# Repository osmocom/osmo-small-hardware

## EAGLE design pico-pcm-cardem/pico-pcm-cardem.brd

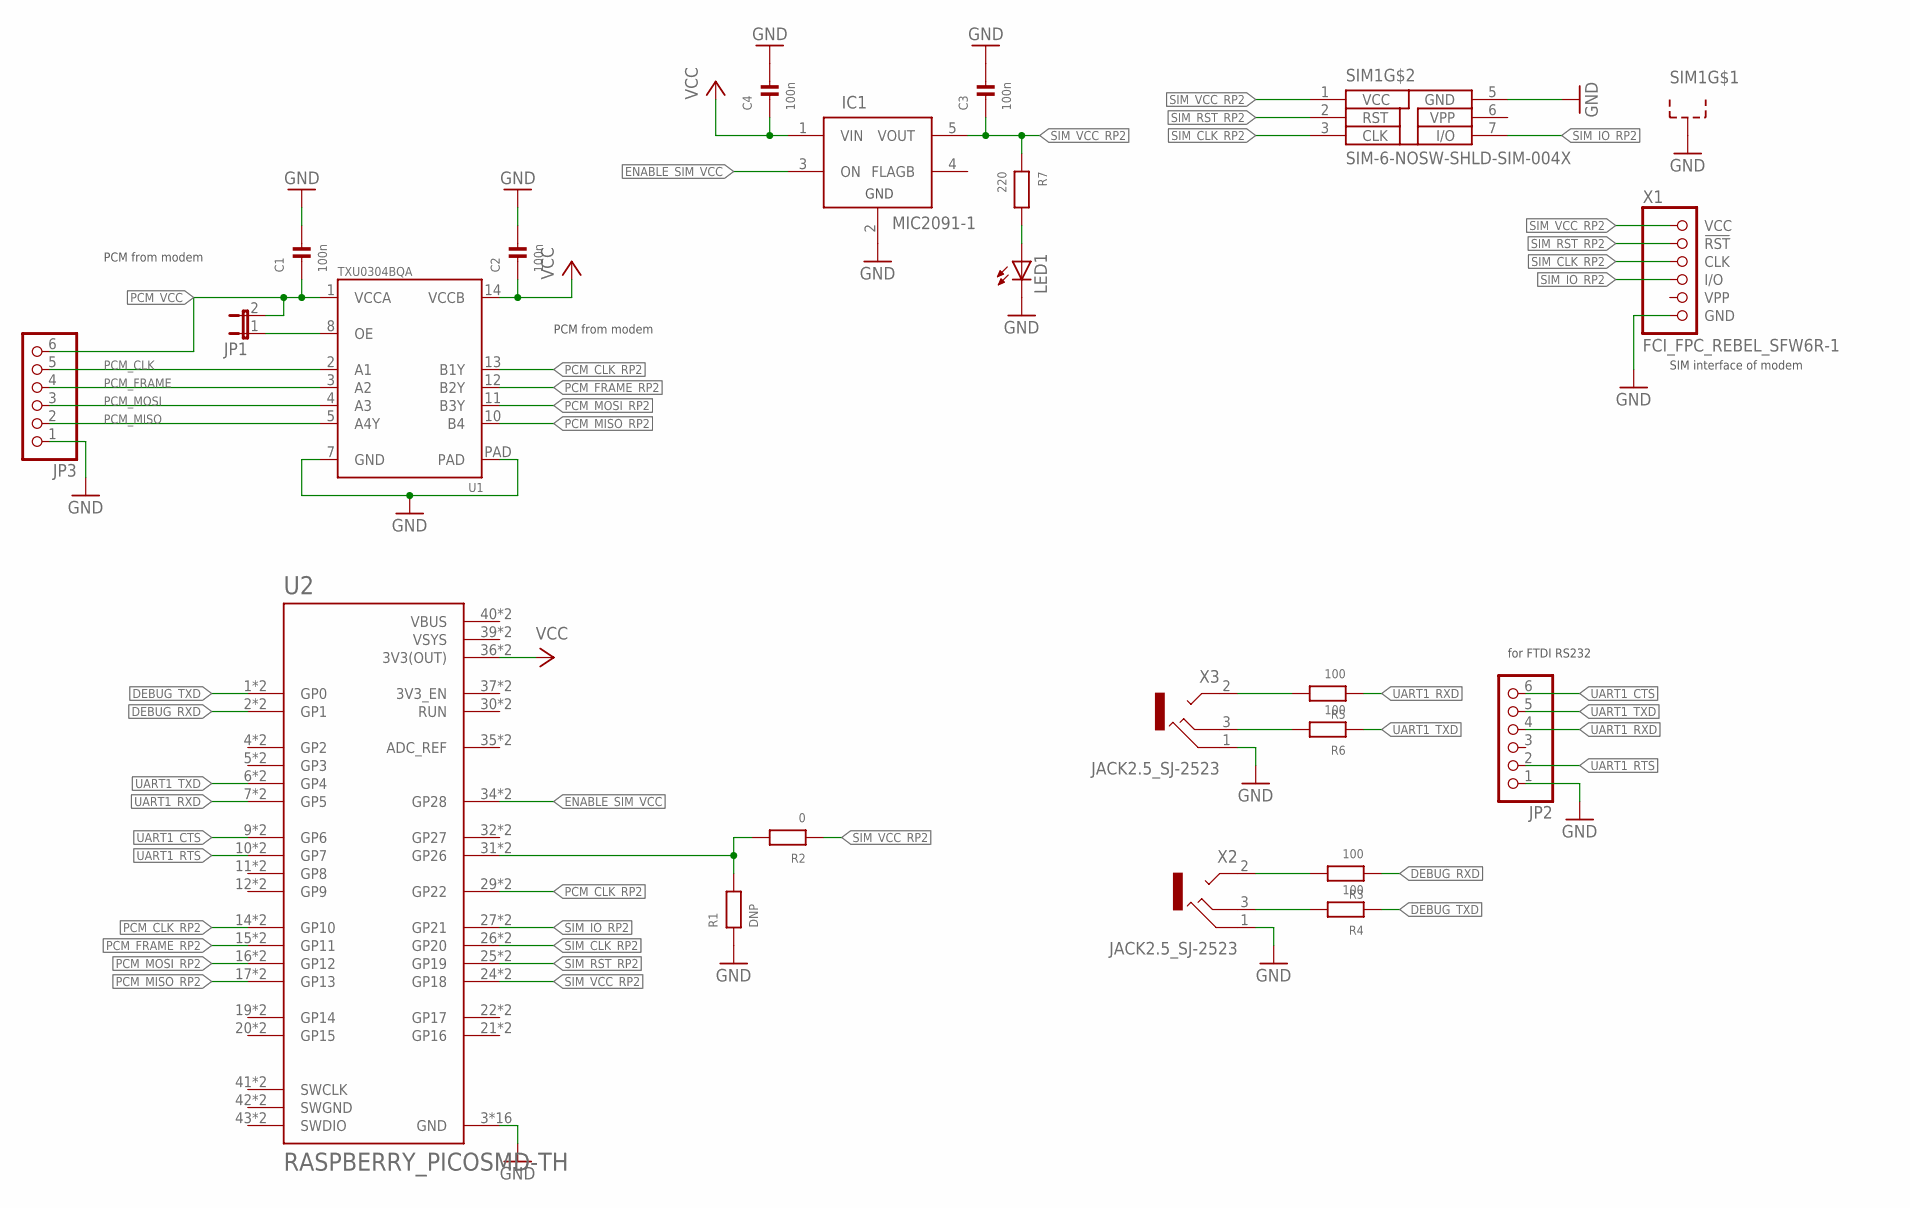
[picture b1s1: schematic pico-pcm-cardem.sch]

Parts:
C1, C2, C3, C4: 100n; _0603; MANUFACTURERPARTNUMBER UNKNOWN MANUFACTURER PART NUMBER
IC1: MIC2091-1; SOT23-5
JP1: JP1E; JP1; MANUFACTURERPARTNUMBER UNKNOWN MANUFACTURER PART NUMBER
JP2, JP3: PINHD-1X6; 1X06; MANUFACTURERPARTNUMBER UNKNOWN MANUFACTURER PART NUMBER
LED1: LEDCHIP-LED0603; CHIP-LED0603; MANUFACTURERPARTNUMBER UNKNOWN MANUFACTURER PART NUMBER
R1: DNP; _0603; MANUFACTURERPARTNUMBER UNKNOWN MANUFACTURER PART NUMBER
R2: 0; _0603; MANUFACTURERPARTNUMBER UNKNOWN MANUFACTURER PART NUMBER
R3, R4, R5, R6: 100; _0603; MANUFACTURERPARTNUMBER UNKNOWN MANUFACTURER PART NUMBER
R7: 220; _0603; MANUFACTURERPARTNUMBER UNKNOWN MANUFACTURER PART NUMBER
SIM1: SIM-6-NOSW-SHLD-SIM-004X; SOFNG_SIM-004X; MANUFACTURERPARTNUMBER UNKNOWN MANUFACTURER PART NUMBER
U1: TXU0304BQA; 14WQFN; MANUFACTURERPARTNUMBER TXU0304BQAR
U2: RASPBERRY_PICOSMD-TH; PICO-PKG; MANUFACTURERPARTNUMBER UNKNOWN MANUFACTURER PART NUMBER
X1: FCI_FPC_REBEL_SFW6R-1; FPC_REBEL_SFW6R-1ST; MANUFACTURERPARTNUMBER SFW6R-1STE1LF
X2: JACK2.5_SJ-2523; MANUFACTURERPARTNUMBER UNKNOWN MANUFACTURER PART NUMBER
X3: JACK2.5_SJ-2523; MANUFACTURERPARTNUMBER SJ-2523-SMT-TR

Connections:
DEBUG_RXD: R3.1, U2.2 (GP1), U2.P$2 (GP1)
DEBUG_TXD: R4.1, U2.1 (GP0), U2.P$1 (GP0)
ENABLE_SIM_VCC: IC1.3 (ON), U2.34 (GP28), U2.P$34 (GP28)
GND: C1.2, C2.2, C3.2, C4.2, IC1.2 (GND), JP2.1, JP3.1, LED1.C, R1.1, SIM1.5 (GND), SIM1.SHLD1 (SHLD), SIM1.SHLD2 (SHLD), SIM1.SHLD3 (SHLD), SIM1.SHLD4 (SHLD), U1.7 (GND), U1.PAD, U2.3 (GND), U2.8 (GND), U2.13 (GND), U2.18 (GND), U2.23 (GND), U2.28 (GND), U2.33 (GND), U2.38 (GND), U2.P$3 (GND), U2.P$8 (GND), U2.P$13 (GND), U2.P$18 (GND), U2.P$23 (GND), U2.P$28 (GND), U2.P$33 (GND), U2.P$38 (GND), X1.6 (GND), X2.1 (RING), X3.1 (RING)
unnamed: R3.2, X2.2 (TIP)
unnamed: JP1.1, U1.8 (OE)
unnamed: R1.2, R2.2, U2.31 (GP26), U2.P$31 (GP26)
unnamed: R4.2, X2.3 (MIDDLE)
unnamed: R5.2, X3.2 (TIP)
unnamed: R6.2, X3.3 (MIDDLE)
unnamed: LED1.A, R7.2
PCM_CLK: JP3.5, U1.2 (A1)
PCM_CLK_RP2: U1.13 (B1Y), U2.14 (GP10), U2.29 (GP22), U2.P$14 (GP10), U2.P$29 (GP22)
PCM_FRAME: JP3.4, U1.3 (A2)
PCM_FRAME_RP2: U1.12 (B2Y), U2.15 (GP11), U2.P$15 (GP11)
PCM_MISO: JP3.2, U1.5 (A4Y)
PCM_MISO_RP2: U1.10 (B4), U2.17 (GP13), U2.P$17 (GP13)
PCM_MOSI: JP3.3, U1.4 (A3)
PCM_MOSI_RP2: U1.11 (B3Y), U2.16 (GP12), U2.P$16 (GP12)
PCM_VCC: C1.1, JP1.2, JP3.6, U1.1 (VCCA)
SIM_CLK_RP2: SIM1.3 (CLK), U2.26 (GP20), U2.P$26 (GP20), X1.3 (CLK)
SIM_IO_RP2: SIM1.7 (I/O), U2.27 (GP21), U2.P$27 (GP21), X1.4 (I/O)
SIM_RST_RP2: SIM1.2 (RST), U2.25 (GP19), U2.P$25 (GP19), X1.2 (!RST)
SIM_VCC_RP2: C3.1, IC1.5 (VOUT), R2.1, R7.1, SIM1.1 (VCC), U2.24 (GP18), U2.P$24 (GP18), X1.1 (VCC)
SWGND: U2.42 (SWGND), U2.P$42 (SWGND)
UART1_CTS: JP2.6, U2.9 (GP6), U2.P$9 (GP6)
UART1_RTS: JP2.2, U2.10 (GP7), U2.P$10 (GP7)
UART1_RXD: JP2.4, R5.1, U2.7 (GP5), U2.P$7 (GP5)
UART1_TXD: JP2.5, R6.1, U2.6 (GP4), U2.P$6 (GP4)
VBUS: U2.40 (VBUS), U2.P$40 (VBUS)
VCC: C2.1, C4.1, IC1.1 (VIN), U1.14 (VCCB), U2.36 (3V3(OUT)), U2.P$36 (3V3(OUT))
VPP: SIM1.6 (VPP), X1.5 (VPP)
VSYS: U2.39 (VSYS), U2.P$39 (VSYS)

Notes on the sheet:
PCM from modem
SIM interface of modem
for FTDI RS232

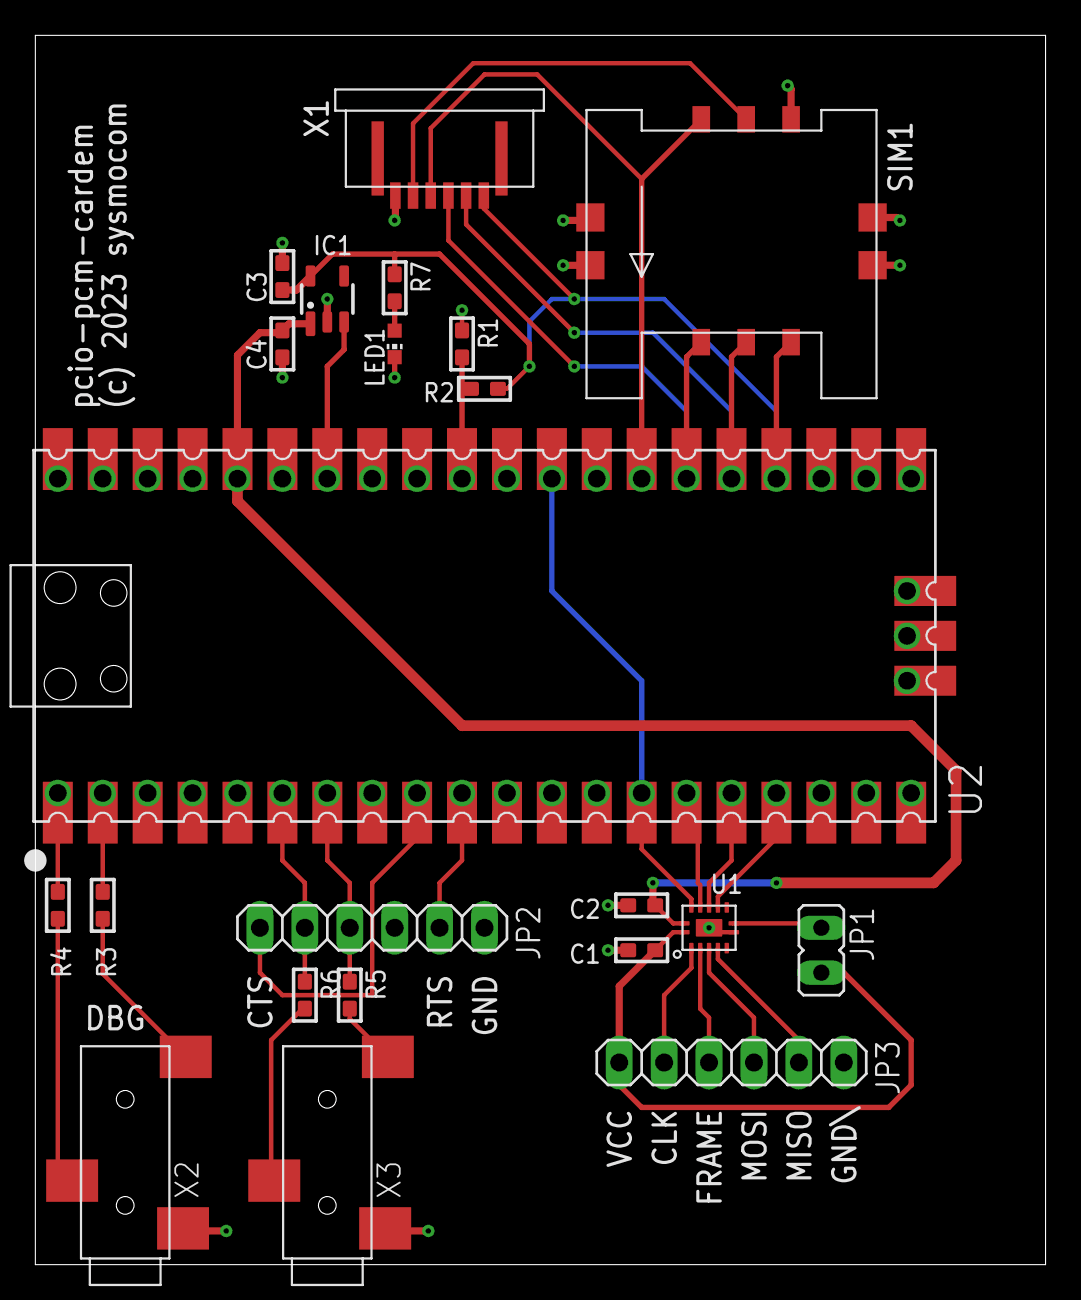
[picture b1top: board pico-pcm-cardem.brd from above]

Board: 2 copper layers, 57.1 x 69.5 mm, 22 parts (0 on the bottom side), 33 nets.

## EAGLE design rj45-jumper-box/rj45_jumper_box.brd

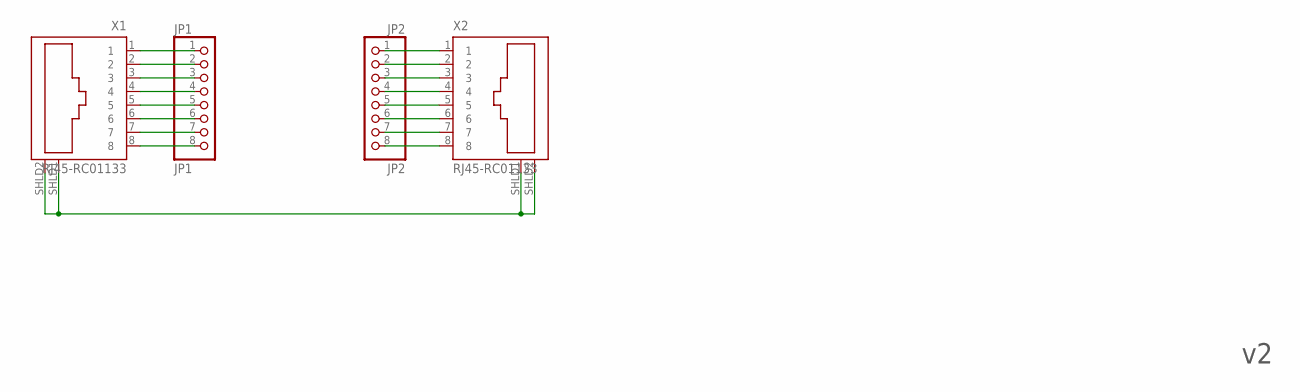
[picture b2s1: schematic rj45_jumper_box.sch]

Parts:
JP1: JP1; 1X08
JP2: JP2; 1X08
X1, X2: RJ45-RC01133; RC01133

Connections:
unnamed: X1.SHLD1 (S1), X1.SHLD2 (S2), X2.SHLD1 (S1), X2.SHLD2 (S2)
unnamed: JP1.2, X1.2
unnamed: JP1.3, X1.3
unnamed: JP1.4, X1.4
unnamed: JP1.5, X1.5
unnamed: JP1.6, X1.6
unnamed: JP1.7, X1.7
unnamed: JP1.8, X1.8
unnamed: JP2.2, X2.2
unnamed: JP2.3, X2.3
unnamed: JP2.4, X2.4
unnamed: JP2.5, X2.5
unnamed: JP2.6, X2.6
unnamed: JP2.7, X2.7
unnamed: JP2.8, X2.8
X1_1: JP1.1, X1.1
X2_1: JP2.1, X2.1

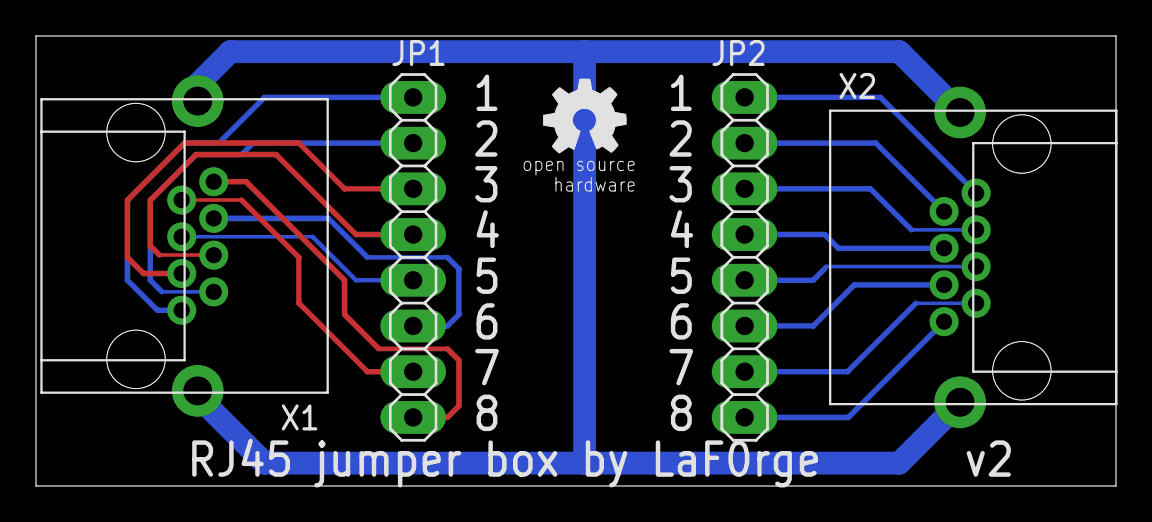
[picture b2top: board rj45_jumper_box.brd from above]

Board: 2 copper layers, 60.0 x 25.0 mm, 6 parts (0 on the bottom side), 17 nets.

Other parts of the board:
U$1: OSHW_5MM
U$2: SYSMOCOM-20-BPLACE

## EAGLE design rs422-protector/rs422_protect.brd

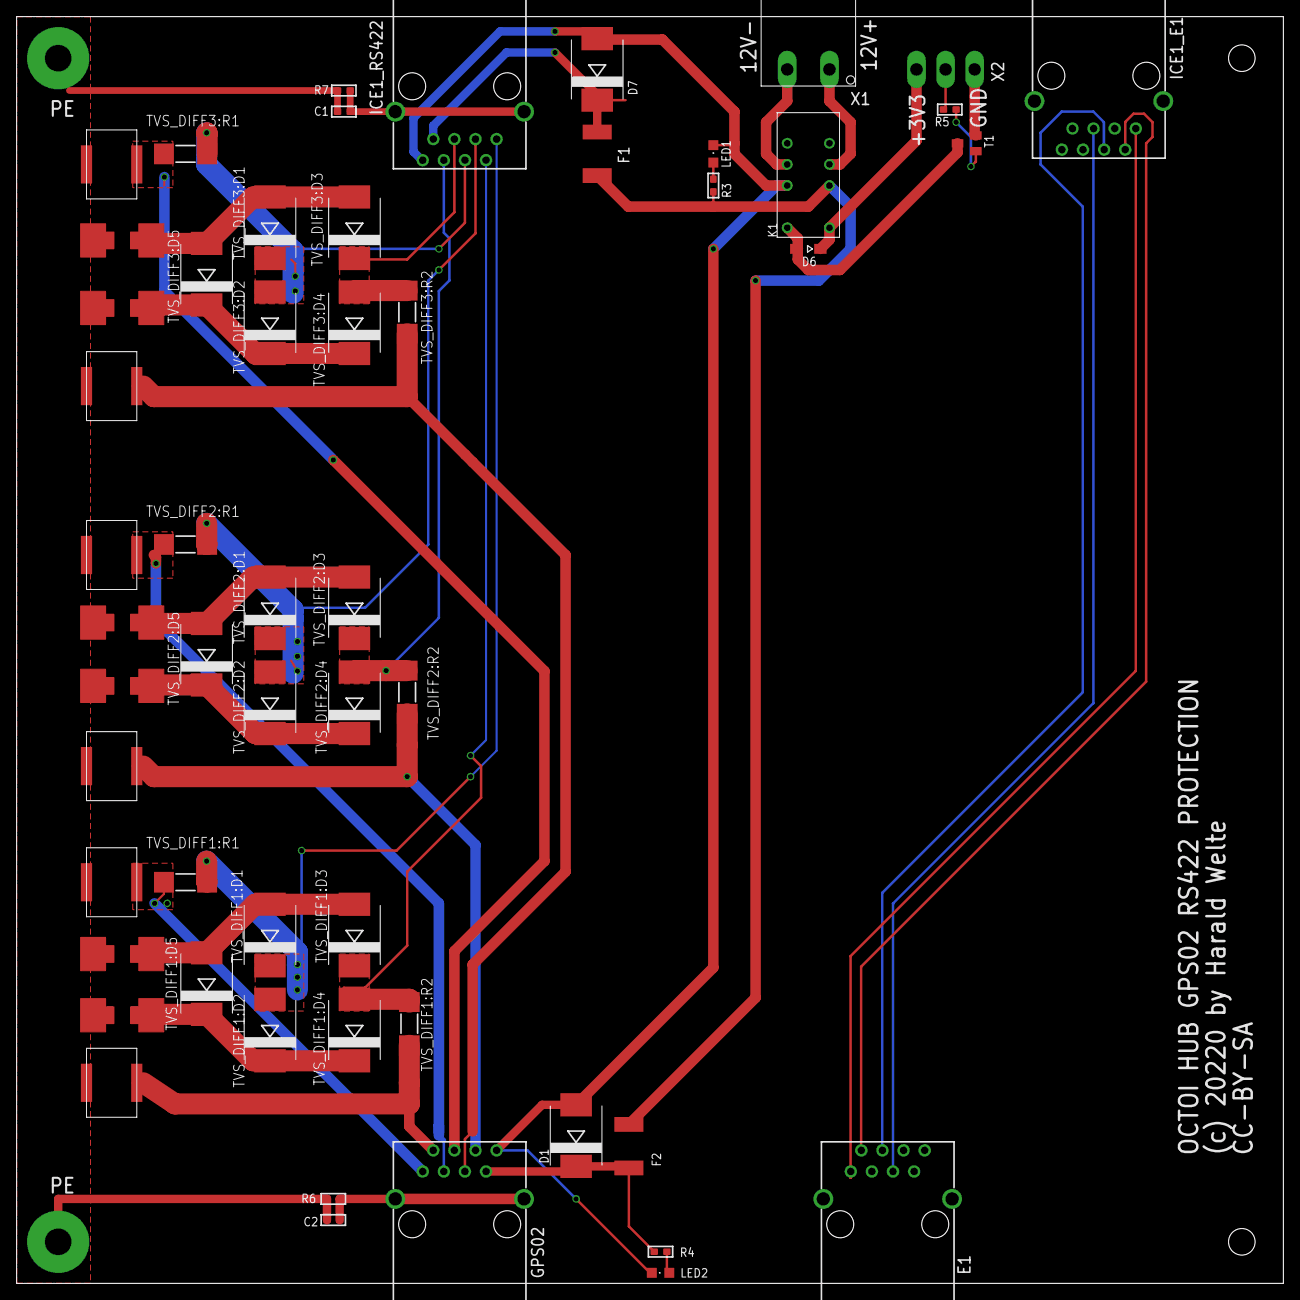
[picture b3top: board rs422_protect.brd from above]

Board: 2 copper layers, 152.4 x 152.4 mm, 55 parts (0 on the bottom side), 38 nets.

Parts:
C1, C2: 100n; _0603
D1, D7: 5.0SMDJ15A; SMC
D6: 1N4148; SOD323-W
E1: SS-7188S-A-NF
F1, F2: 1812
GPS02: SS-7188S-A-NF
ICE1_E1, ICE1_RS422: SS-7188S-A-NF
K1: EC2-3NU; EC2-SINGLECOIL
LED1, LED2: CHIPLED_0805
R3, R4, R5: _0603
R6, R7: 1M; _0603
T1: BC847; SOT23
TVS_DIFF1:A1, TVS_DIFF1:A2, TVS_DIFF2:A1, TVS_DIFF2:A2, TVS_DIFF3:A1, TVS_DIFF3:A2: EPCOS_SURGE_ARRESTOR
TVS_DIFF1:D1, TVS_DIFF1:D2, TVS_DIFF1:D3, TVS_DIFF1:D4, TVS_DIFF2:D1, TVS_DIFF2:D2, TVS_DIFF2:D3, TVS_DIFF2:D4, TVS_DIFF3:D1, TVS_DIFF3:D2, TVS_DIFF3:D3, TVS_DIFF3:D4: 5.0SMDJ9.0A; SMC
TVS_DIFF1:D5, TVS_DIFF2:D5, TVS_DIFF3:D5: SMCJ8.5CA-HR; SMC
TVS_DIFF1:R1, TVS_DIFF1:R2, TVS_DIFF2:R1, TVS_DIFF2:R2, TVS_DIFF3:R1, TVS_DIFF3:R2: 1R8; MINI_MELF-0207W
TVS_DIFF1:U$1, TVS_DIFF1:U$2, TVS_DIFF2:U$1, TVS_DIFF2:U$2, TVS_DIFF3:U$1, TVS_DIFF3:U$2: ARCGAP-2MM; ARC_GAP
X1: RIA230
X2: RIA182-03

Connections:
3.3V: D6.C, K1.1, X2.3
12VGND_IN: K1.9, X1.2
12VGND_OUT: D1.A, D7.A, GPS02.8, ICE1_RS422.8, K1.10, LED1.C, LED2.C
12V_GPS02: D1.C, F2.1, GPS02.7, R4.2
12V_ICE1: D7.C, F1.1, ICE1_RS422.7
12V_IN: K1.4, X1.1
12V_SWITCHED: F1.2, F2.2, K1.3, R3.2
AGND: C1.1, C2.1, R6.1, R7.1, TVS_DIFF1:A1.2, TVS_DIFF1:A2.2, TVS_DIFF1:U$1.P$1, TVS_DIFF1:U$2.P$1, TVS_DIFF2:A1.2, TVS_DIFF2:A2.2, TVS_DIFF2:U$1.P$1, TVS_DIFF2:U$2.P$1, TVS_DIFF3:A1.2, TVS_DIFF3:A2.2, TVS_DIFF3:U$1.P$1, TVS_DIFF3:U$2.P$1
unnamed: GPS02.1, TVS_DIFF1:A1.1, TVS_DIFF1:R1.1
unnamed: GPS02.2, TVS_DIFF1:A2.1, TVS_DIFF1:R2.1
unnamed: D6.A, K1.12, T1.3
unnamed: C2.2, GPS02.S1, GPS02.S2, R6.2
unnamed: R5.2, T1.1
unnamed: C1.2, ICE1_RS422.S1, ICE1_RS422.S2, R7.2
unnamed: LED1.A, R3.1
unnamed: LED2.A, R4.1
unnamed: R5.1, X2.2
unnamed: GPS02.3, TVS_DIFF2:A1.1, TVS_DIFF2:R1.1
unnamed: GPS02.6, TVS_DIFF2:A2.1, TVS_DIFF2:R2.1
unnamed: T1.2, X2.1
unnamed: GPS02.4, TVS_DIFF3:A1.1, TVS_DIFF3:R1.1
unnamed: GPS02.5, TVS_DIFF3:A2.1, TVS_DIFF3:R2.1
unnamed: ICE1_RS422.1, TVS_DIFF1:D1.C, TVS_DIFF1:D2.A, TVS_DIFF1:R1.2
unnamed: ICE1_RS422.2, TVS_DIFF1:D3.C, TVS_DIFF1:D4.A, TVS_DIFF1:R2.2
unnamed: ICE1_RS422.3, TVS_DIFF2:D1.C, TVS_DIFF2:D2.A, TVS_DIFF2:R1.2
unnamed: ICE1_RS422.6, TVS_DIFF2:D3.C, TVS_DIFF2:D4.A, TVS_DIFF2:R2.2
unnamed: ICE1_RS422.4, TVS_DIFF3:D1.C, TVS_DIFF3:D2.A, TVS_DIFF3:R1.2
unnamed: ICE1_RS422.5, TVS_DIFF3:D3.C, TVS_DIFF3:D4.A, TVS_DIFF3:R2.2
unnamed: E1.1, ICE1_E1.1
unnamed: E1.2, ICE1_E1.2
unnamed: E1.4, ICE1_E1.4
unnamed: E1.5, ICE1_E1.5
TVS_DIFF1:N$1: TVS_DIFF1:D1.A, TVS_DIFF1:D3.A, TVS_DIFF1:D5.A, TVS_DIFF1:U$1.P$2
TVS_DIFF1:N$2: TVS_DIFF1:D2.C, TVS_DIFF1:D4.C, TVS_DIFF1:D5.C, TVS_DIFF1:U$2.P$2
TVS_DIFF2:N$1: TVS_DIFF2:D1.A, TVS_DIFF2:D3.A, TVS_DIFF2:D5.A, TVS_DIFF2:U$1.P$2
TVS_DIFF2:N$2: TVS_DIFF2:D2.C, TVS_DIFF2:D4.C, TVS_DIFF2:D5.C, TVS_DIFF2:U$2.P$2
TVS_DIFF3:N$1: TVS_DIFF3:D1.A, TVS_DIFF3:D3.A, TVS_DIFF3:D5.A, TVS_DIFF3:U$1.P$2
TVS_DIFF3:N$2: TVS_DIFF3:D2.C, TVS_DIFF3:D4.C, TVS_DIFF3:D5.C, TVS_DIFF3:U$2.P$2

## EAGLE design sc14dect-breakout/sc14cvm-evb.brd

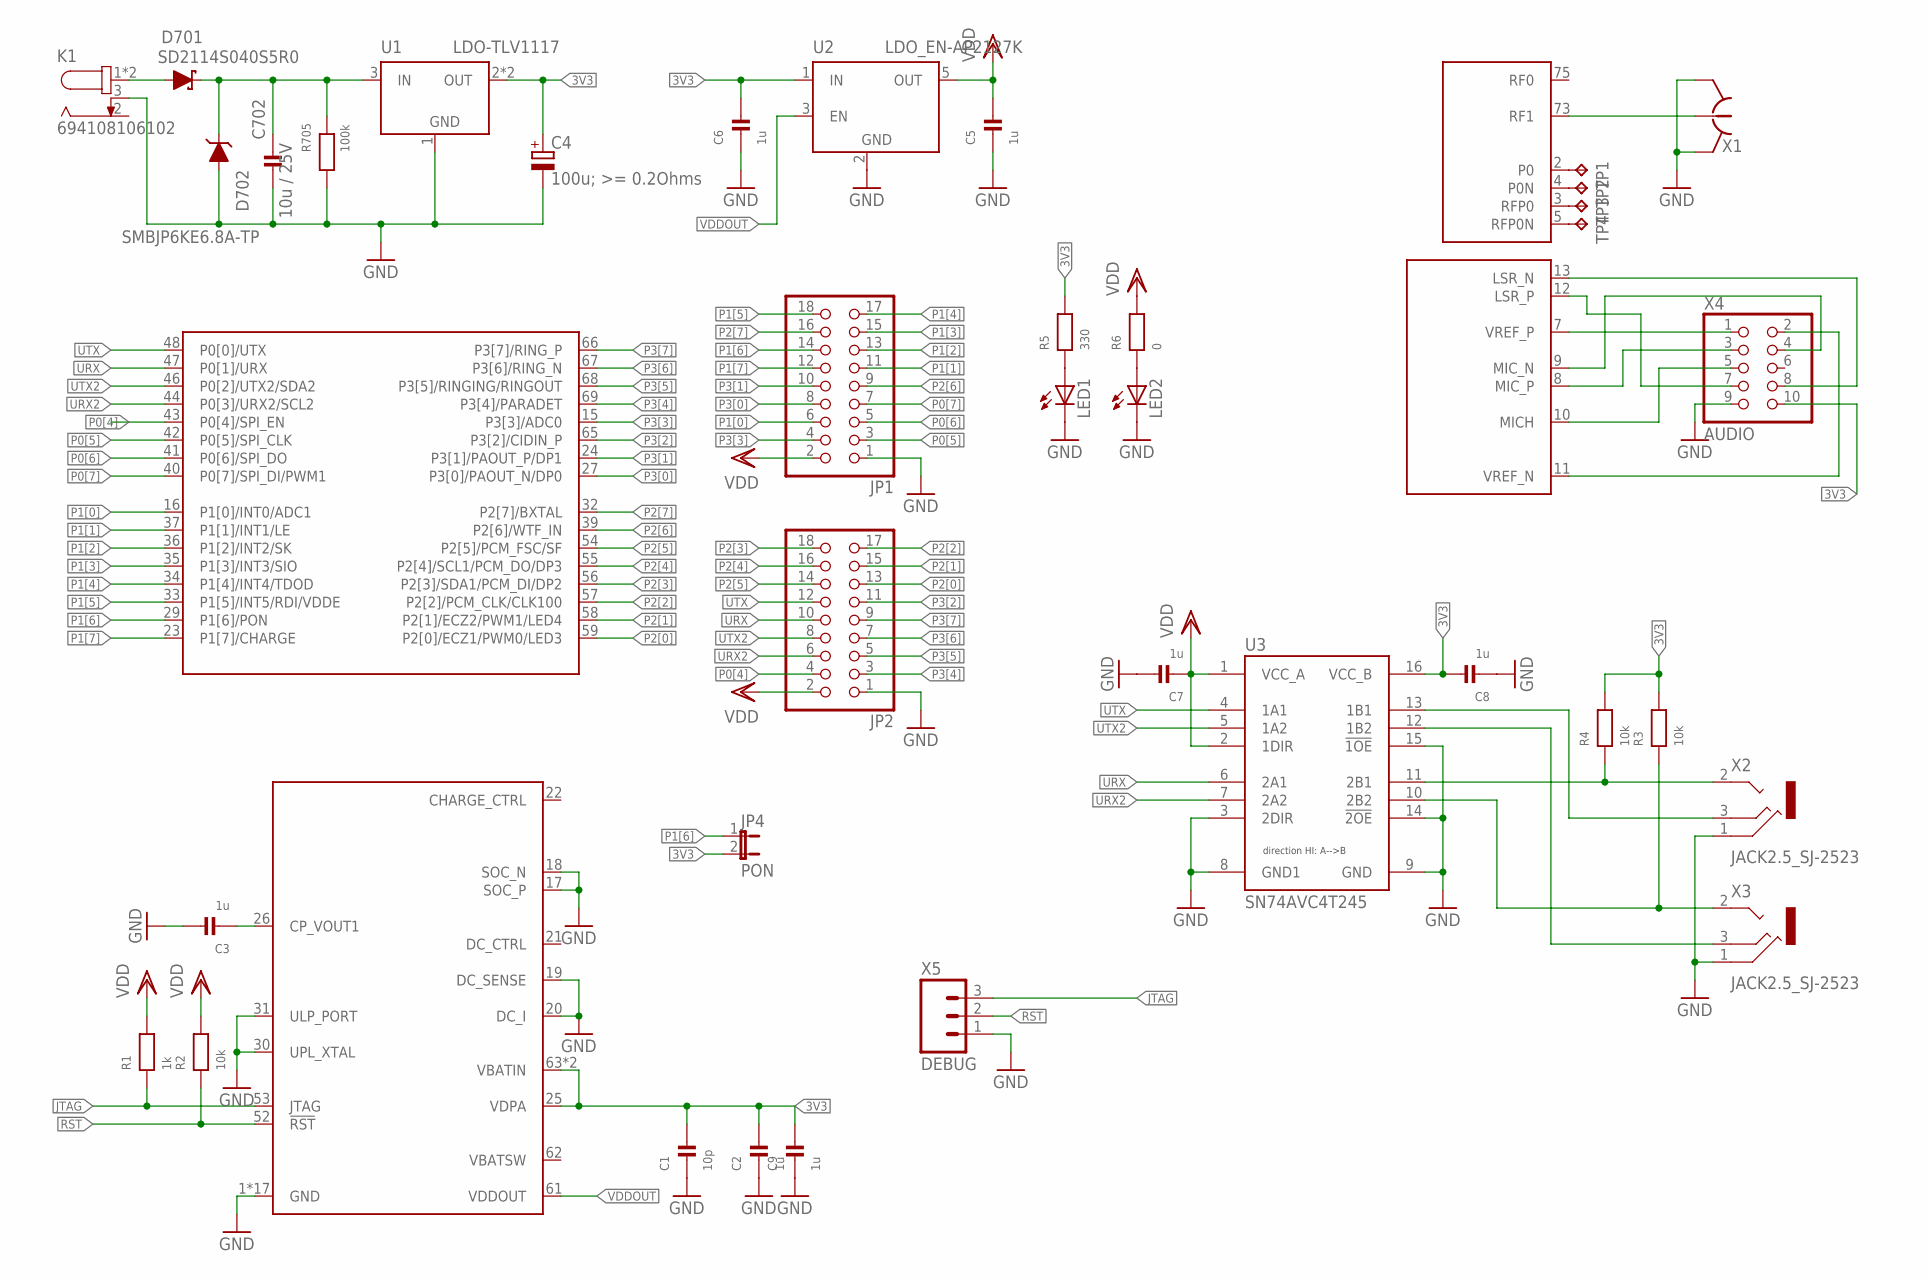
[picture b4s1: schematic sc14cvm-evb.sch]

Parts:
C1: 10p; _0402; MANUFACTURERPARTNUMBER UNKNOWN MANUFACTURER PART NUMBER
C2, C9: 1u; _0402; MANUFACTURERPARTNUMBER UNKNOWN MANUFACTURER PART NUMBER
C3, C5, C6, C7, C8: 1u; _0603; MANUFACTURERPARTNUMBER UNKNOWN MANUFACTURER PART NUMBER
C4: 100u; >= 0.2Ohms; SMC_B; MANUFACTURERPARTNUMBER UNKNOWN MANUFACTURER PART NUMBER
C702: 10u / 25V; C1812K; MANUFACTURERPARTNUMBER C4532X7R1E106M250KA
D701: SD2114S040S5R0; SMBDIODE; MANUFACTURERPARTNUMBER SD2114S040S5R0
D702: SMBJP6KE6.8A-TP; SMBDIODE; MANUFACTURERPARTNUMBER SMBJP6KE6.8A-TP
JP1, JP2: PINHD-2X9; 2X09; MANUFACTURERPARTNUMBER UNKNOWN MANUFACTURER PART NUMBER
JP4: PON; JP1; MANUFACTURERPARTNUMBER UNKNOWN MANUFACTURER PART NUMBER
K1: 694108106102; MANUFACTURERPARTNUMBER UNKNOWN MANUFACTURER PART NUMBER
LED1, LED2: LEDCHIPLED_0603; CHIPLED_0603; MANUFACTURERPARTNUMBER UNKNOWN MANUFACTURER PART NUMBER
MOD1: SC14CVMDECT; MOD88; MANUFACTURERPARTNUMBER UNKNOWN MANUFACTURER PART NUMBER
R1: 1k; _0603@2; MANUFACTURERPARTNUMBER UNKNOWN MANUFACTURER PART NUMBER
R2, R3, R4: 10k; _0603@2; MANUFACTURERPARTNUMBER UNKNOWN MANUFACTURER PART NUMBER
R5: 330; _0603@2; MANUFACTURERPARTNUMBER UNKNOWN MANUFACTURER PART NUMBER
R6: 0; _0603@2; MANUFACTURERPARTNUMBER UNKNOWN MANUFACTURER PART NUMBER
R705: 100k; _0603@2; MANUFACTURERPARTNUMBER CRCW0603100KFKEA
TP1, TP2, TP3, TP4: TPTP11R; TP11R; MANUFACTURERPARTNUMBER UNKNOWN MANUFACTURER PART NUMBER
U1: LDO-TLV1117; SOT223; MANUFACTURERPARTNUMBER UNKNOWN MANUFACTURER PART NUMBER
U2: LDO_EN-AP2127K; SOT23L; MANUFACTURERPARTNUMBER AP2127K-1.8TRG1
U3: SN74AVC4T245; TSSOP16; MANUFACTURERPARTNUMBER UNKNOWN MANUFACTURER PART NUMBER
X1: HRS_UFL; MANUFACTURERPARTNUMBER UNKNOWN MANUFACTURER PART NUMBER
X2, X3: JACK2.5_SJ-2523; MANUFACTURERPARTNUMBER UNKNOWN MANUFACTURER PART NUMBER
X4: AUDIO; 2X05; MANUFACTURERPARTNUMBER UNKNOWN MANUFACTURER PART NUMBER
X5: DEBUG; 1X03_LOCK_LONGPADS; MANUFACTURERPARTNUMBER UNKNOWN MANUFACTURER PART NUMBER

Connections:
3V3: C1.2, C2.2, C4.+, C6.2, C8.2, C9.2, JP4.2, MOD1.25 (VDPA), MOD1.63 (VBATIN), MOD1.64 (VBATIN), R3.2, R4.2, R5.2, U1.2 (OUT), U1.4 (OUT), U2.1 (IN), U3.16 (VCC_B), X4.10
!RST: MOD1.52 (!RST), R2.1, X5.2
+VIN_PROT: C702.1, D701.C, D702.C, R705.2, U1.3 (IN)
GND: C1.1, C2.1, C3.2, C4.-, C5.1, C6.1, C7.2, C8.1, C9.1, C702.2, D702.A, JP1.1, JP2.1, K1.3, LED1.C, LED2.C, MOD1.1 (GND), MOD1.6 (GND), MOD1.14 (GND), MOD1.17 (SOC_P), MOD1.18 (SOC_N), MOD1.19 (DC_SENSE), MOD1.20 (DC_I), MOD1.28 (GND), MOD1.30 (UPL_XTAL), MOD1.31 (ULP_PORT), MOD1.38 (GND), MOD1.45 (GND), MOD1.49 (GND), MOD1.50 (GND), MOD1.51 (GND), MOD1.60 (GND), MOD1.70 (GND), MOD1.71 (GND), MOD1.72 (GND), MOD1.74 (GND), MOD1.76 (GND), MOD1.77 (GND), MOD1.78 (GND), R705.1, U1.1 (GND), U2.2 (GND), U3.3 (2DIR), U3.8 (GND1), U3.9 (GND), U3.14 (!2OE), U3.15 (!1OE), X1.GND@1 (GND), X1.GND@2 (GND), X2.1 (RING), X3.1 (RING), X4.9, X5.1
JTAG: MOD1.53 (JTAG), R1.1, X5.3
unnamed: D701.A, K1.1, K1.1-1 (1)
unnamed: MOD1.7 (VREF_P), X4.1
unnamed: C3.1, MOD1.26 (CP_VOUT1)
unnamed: MOD1.11 (VREF_N), X4.2
unnamed: MOD1.8 (MIC_P), X4.3
unnamed: MOD1.9 (MIC_N), X4.4
unnamed: MOD1.12 (LSR_P), X4.7
unnamed: MOD1.13 (LSR_N), X4.8
unnamed: MOD1.10 (MICH), X4.5
unnamed: MOD1.2 (P0), TP1.TP
unnamed: MOD1.4 (P0N), TP2.TP
unnamed: MOD1.3 (RFP0), TP3.TP
unnamed: MOD1.5 (RFP0N), TP4.TP
unnamed: LED1.A, R5.1
unnamed: LED2.A, R6.1
P0[4]: JP2.4, MOD1.43 (P0[4]/SPI_EN)
P0[5]: JP1.3, MOD1.42 (P0[5]/SPI_CLK)
P0[6]: JP1.5, MOD1.41 (P0[6]/SPI_DO)
P0[7]: JP1.7, MOD1.40 (P0[7]/SPI_DI/PWM1)
P1[0]: JP1.6, MOD1.16 (P1[0]/INT0/ADC1)
P1[1]: JP1.11, MOD1.37 (P1[1]/INT1/LE)
P1[2]: JP1.13, MOD1.36 (P1[2]/INT2/SK)
P1[3]: JP1.15, MOD1.35 (P1[3]/INT3/SIO)
P1[4]: JP1.17, MOD1.34 (P1[4]/INT4/TDOD)
P1[5]: JP1.18, MOD1.33 (P1[5]/INT5/RDI/VDDE)
P1[6]: JP1.14, JP4.1, MOD1.29 (P1[6]/PON)
P1[7]: JP1.12, MOD1.23 (P1[7]/CHARGE)
P2[0]: JP2.13, MOD1.59 (P2[0]/ECZ1/PWM0/LED3)
P2[1]: JP2.15, MOD1.58 (P2[1]/ECZ2/PWM1/LED4)
P2[2]: JP2.17, MOD1.57 (P2[2]/PCM_CLK/CLK100)
P2[3]: JP2.18, MOD1.56 (P2[3]/SDA1/PCM_DI/DP2)
P2[4]: JP2.16, MOD1.55 (P2[4]/SCL1/PCM_DO/DP3)
P2[5]: JP2.14, MOD1.54 (P2[5]/PCM_FSC/SF)
P2[6]: JP1.9, MOD1.39 (P2[6]/WTF_IN)
P2[7]: JP1.16, MOD1.32 (P2[7]/BXTAL)
P3[0]: JP1.8, MOD1.27 (P3[0]/PAOUT_N/DP0)
P3[1]: JP1.10, MOD1.24 (P3[1]/PAOUT_P/DP1)
P3[2]: JP2.11, MOD1.65 (P3[2]/CIDIN_P)
P3[3]: JP1.4, MOD1.15 (P3[3]/ADC0)
P3[4]: JP2.3, MOD1.69 (P3[4]/PARADET)
P3[5]: JP2.5, MOD1.68 (P3[5]/RINGING/RINGOUT)
P3[6]: JP2.7, MOD1.67 (P3[6]/RING_N)
P3[7]: JP2.9, MOD1.66 (P3[7]/RING_P)
RF1: MOD1.73 (RF1), X1.SIG (1)
URX: JP2.10, MOD1.47 (P0[1]/URX), U3.6 (2A1)
URX2: JP2.6, MOD1.44 (P0[3]/URX2/SCL2), U3.7 (2A2)
URX2_3V3: R3.1, U3.10 (2B2), X3.2 (TIP)
URX_3V3: R4.1, U3.11 (2B1), X2.2 (TIP)
UTX: JP2.12, MOD1.48 (P0[0]/UTX), U3.4 (1A1)
UTX2: JP2.8, MOD1.46 (P0[2]/UTX2/SDA2), U3.5 (1A2)
UTX2_3V3: U3.12 (1B2), X3.3 (MIDDLE)
UTX_3V3: U3.13 (1B1), X2.3 (MIDDLE)
VDD: C5.2, C7.1, JP1.2, JP2.2, R1.2, R2.2, R6.2, U2.5 (OUT), U3.1 (VCC_A), U3.2 (1DIR)
VDDOUT: MOD1.61 (VDDOUT), U2.3 (EN)

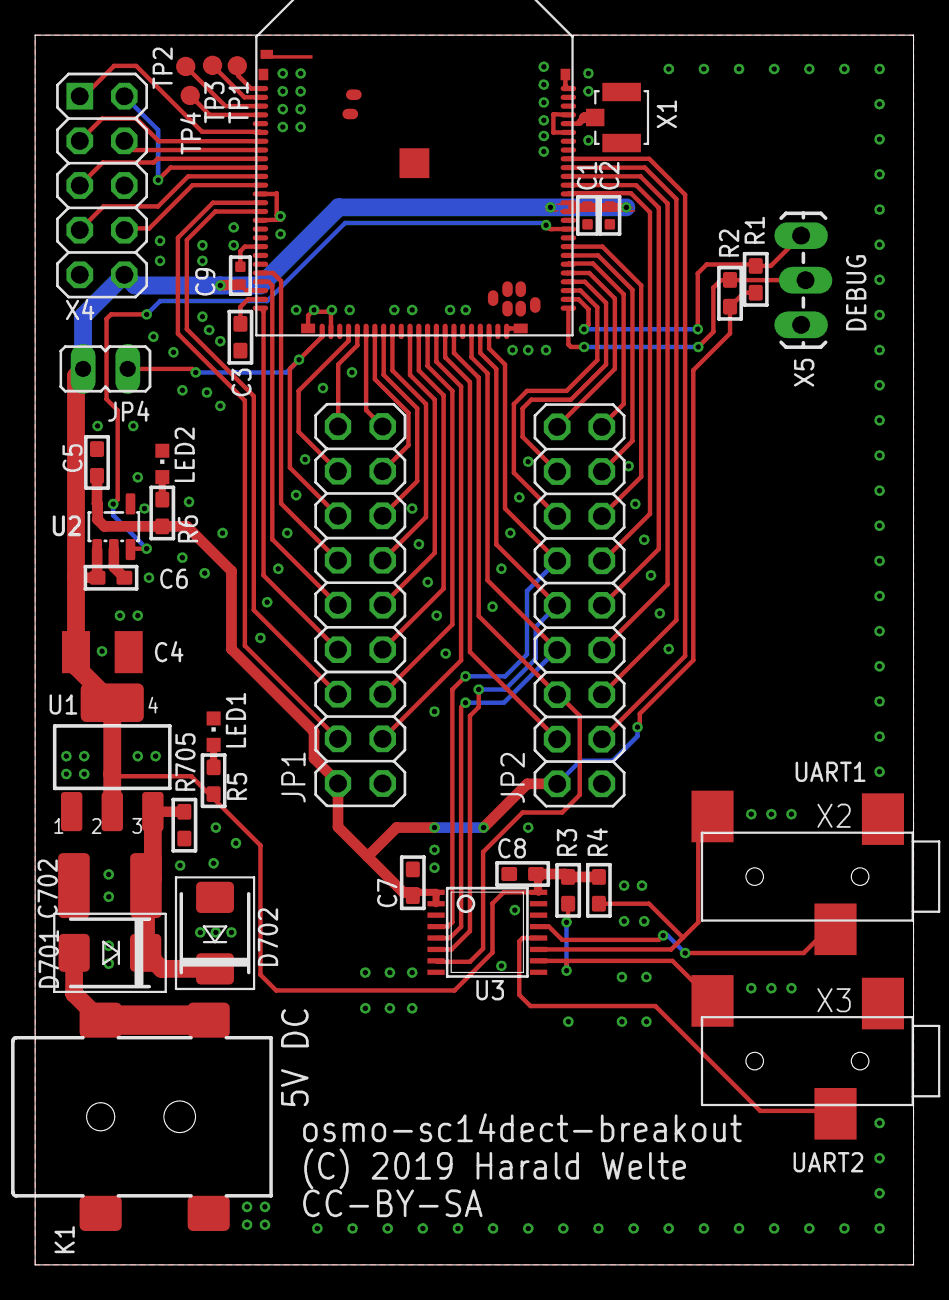
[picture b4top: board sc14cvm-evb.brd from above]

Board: 2 copper layers, 50.0 x 70.0 mm, 38 parts (0 on the bottom side), 59 nets.

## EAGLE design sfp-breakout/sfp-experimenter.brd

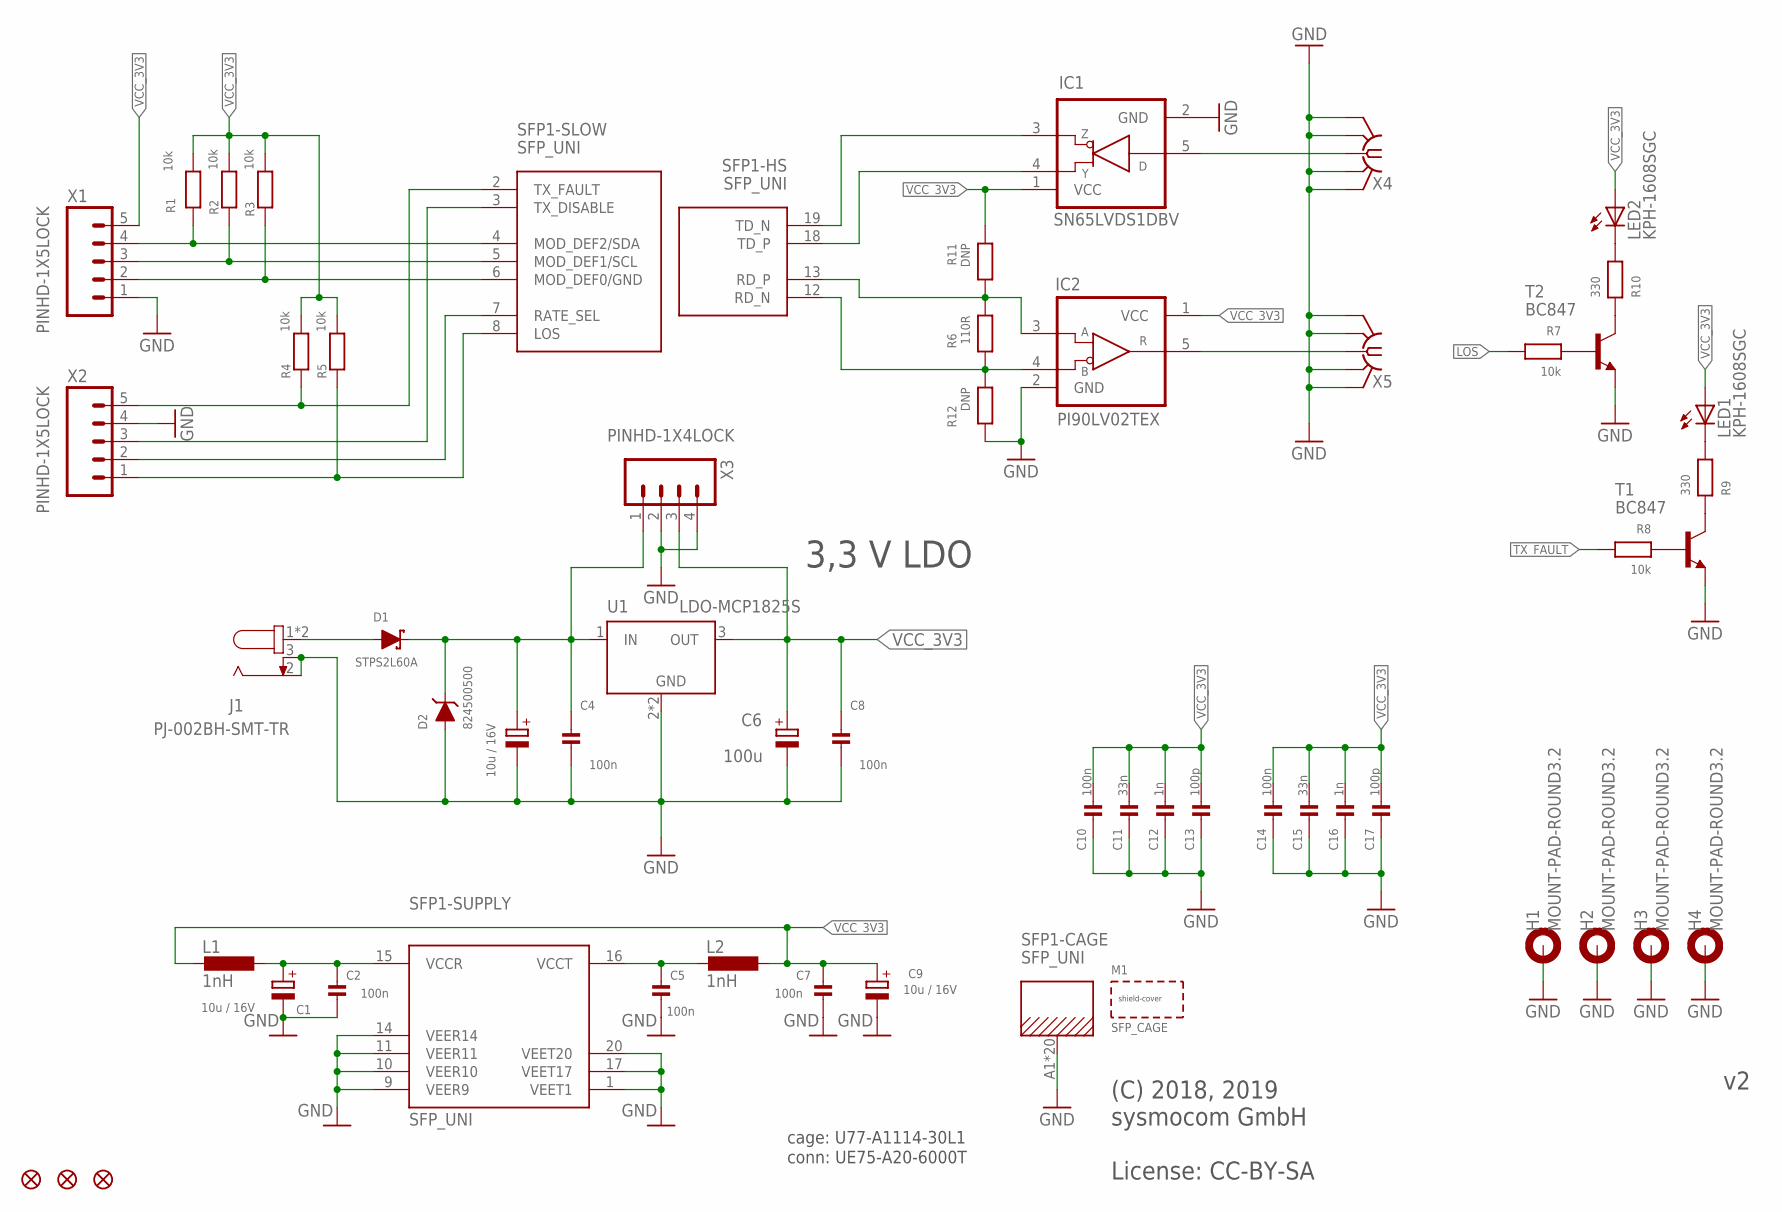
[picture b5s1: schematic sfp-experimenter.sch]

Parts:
C1, C3, C9: 10u / 16V; CPOL1206; MANUFACTURERPARTNUMBER CL31A106KOHNNNE
C2, C4, C5, C7, C8, C10, C14: 100n; _0603; MANUFACTURERPARTNUMBER CL10B104KO8NNNC
C6: 100u; CT6032; MANUFACTURERPARTNUMBER T520C107M006ATE045
C11, C15: 33n; _0603; MANUFACTURERPARTNUMBER 06035C333JAT2A
C12, C16: 1n; _0603; MANUFACTURERPARTNUMBER CC0603KRX7R9BB102
C13, C17: 100p; _0603; MANUFACTURERPARTNUMBER CC0603JRNPO9BN101
D1: STPS2L60A; SMADIODE; MANUFACTURERPARTNUMBER STPS2L60A
D2: 824500500; SMADIODE; MANUFACTURERPARTNUMBER SMAJ5.0A
FID1, FID2, FID3: FIDUCIAL1X2.5; FIDUCIAL-1X2.5
H1, H2, H3, H4: MOUNT-PAD-ROUND3.2; 3,2-PAD; MANUFACTURERPARTNUMBER UNKNOWN MANUFACTURER PART NUMBER
IC1: SN65LVDS1DBV; SOT23-5; MANUFACTURERPARTNUMBER SN65LVDS1DBVR
IC2: PI90LV02TEX; SOT23-5; MANUFACTURERPARTNUMBER PI90LV02TEX
J1: PJ-002BH-SMT-TR; 694108106102; MANUFACTURERPARTNUMBER PJ-002BH-SMT-TR
L1, L2: 1nH; 0603; MANUFACTURERPARTNUMBER AIMC-0603-1N0S-T
LED1, LED2: KPH-1608SGC; CHIP-LED0603; MANUFACTURERPARTNUMBER UNKNOWN MANUFACTURER PART NUMBER
R1, R2, R3, R4, R5, R7, R8: 10k; _0603; MANUFACTURERPARTNUMBER RC0603FR-0710KL
R6: 110R; _0402; MANUFACTURERPARTNUMBER RC0603FR-13110RL
R9, R10: 330; _0603; MANUFACTURERPARTNUMBER ERJ-3GEYJ331V
R11: DNP; _0603; MANUFACTURERPARTNUMBER UNKNOWN MANUFACTURER PART NUMBER
R12: DNP; _0603; MANUFACTURERPARTNUMBER RK73H1JTTD1003F
SFP1: SFP_UNI; SFP_COMBINED; MANUFACTURERPARTNUMBER UE75-A20-6000T
T1, T2: BC847; SOT23-BEC; MANUFACTURERPARTNUMBER BC847C,215
U1: LDO-MCP1825S; SOT223; MANUFACTURERPARTNUMBER MCP1825ST-3302E/DB
X1, X2: PINHD-1X5LOCK; 1X05_LOCK; MANUFACTURERPARTNUMBER UNKNOWN MANUFACTURER PART NUMBER
X3: PINHD-1X4LOCK; 1X04_LOCK; MANUFACTURERPARTNUMBER UNKNOWN MANUFACTURER PART NUMBER
X4, X5: SMA-F-S-EDGE; MANUFACTURERPARTNUMBER UNKNOWN MANUFACTURER PART NUMBER

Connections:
+VIN1: C3.+, C4.1, D1.C, D2.C, U1.1 (IN), X3.1
GND: C1.-, C2.2, C3.-, C4.2, C5.2, C6.-, C7.2, C8.2, C9.-, C10.2, C11.2, C12.2, C13.2, C14.2, C15.2, C16.2, C17.2, D2.A, H1.B3,2, H2.B3,2, H3.B3,2, H4.B3,2, IC1.2 (GND), IC2.2 (GND), J1.2, J1.3, R12.2, SFP1.1 (VEET1), SFP1.9 (VEER9), SFP1.10 (VEER10), SFP1.11 (VEER11), SFP1.14 (VEER14), SFP1.17 (VEET17), SFP1.20 (VEET20), SFP1.A1 (CAGE), SFP1.A2 (CAGE), SFP1.A3 (CAGE), SFP1.A4 (CAGE), SFP1.A5 (CAGE), SFP1.A6 (CAGE), SFP1.A7 (CAGE), SFP1.A8 (CAGE), SFP1.A10 (CAGE), SFP1.A11 (CAGE), SFP1.A12 (CAGE), SFP1.B1 (CAGE), SFP1.B2 (CAGE), SFP1.B3 (CAGE), SFP1.B4 (CAGE), SFP1.B5 (CAGE), SFP1.B6 (CAGE), SFP1.B7 (CAGE), SFP1.B8 (CAGE), SFP1.B10 (CAGE), T1.E, T2.E, U1.2 (GND), U1.4 (GND), X1.1, X2.4, X3.2, X3.4, X4.BG1 (GND), X4.BG2 (GND), X4.TG1 (GND), X4.TG2 (GND), X5.BG1 (GND), X5.BG2 (GND), X5.TG1 (GND), X5.TG2 (GND)
LOS: R5.1, R7.2, SFP1.8 (LOS), X2.1
MOD_DEF0/GND: R3.1, SFP1.6 (MOD_DEF0/GND), X1.2
MOD_DEF1/SCL: R2.1, SFP1.5 (MOD_DEF1/SCL), X1.3
MOD_DEF2/SDA: R1.1, SFP1.4 (MOD_DEF2/SDA), X1.4
unnamed: D1.A, J1.1, J1.1-1 (1)
unnamed: R7.1, T2.B
unnamed: LED2.C, R10.2
unnamed: C5.1, L2.2, SFP1.16 (VCCT)
unnamed: C1.+, C2.1, L1.1, SFP1.15 (VCCR)
unnamed: R10.1, T2.C
unnamed: R8.1, T1.B
unnamed: LED1.C, R9.2
unnamed: R9.1, T1.C
RATE_SEL: SFP1.7 (RATE_SEL), X2.2
RD: IC2.5 (R), X5.C (1)
RD_N: IC2.4 (B), R6.2, R12.1, SFP1.12 (RD_N)
RD_P: IC2.3 (A), R6.1, R11.2, SFP1.13 (RD_P)
TD: IC1.5 (D), X4.C (1)
TD_N: IC1.3 (Z), SFP1.19 (TD_N)
TD_P: IC1.4 (Y), SFP1.18 (TD_P)
TX_DISABLE: SFP1.3 (TX_DISABLE), X2.3
TX_FAULT: R4.1, R8.2, SFP1.2 (TX_FAULT), X2.5
VCC_3V3: C6.+, C7.1, C8.1, C9.+, C10.1, C11.1, C12.1, C13.1, C14.1, C15.1, C16.1, C17.1, IC1.1 (VCC), IC2.1 (VCC), L1.2, L2.1, LED1.A, LED2.A, R1.2, R2.2, R3.2, R4.2, R5.2, R11.1, U1.3 (OUT), X1.5, X3.3

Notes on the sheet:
(C) 2018, 2019 sysmocom GmbH License: CC-BY-SA
3,3 V LDO
cage: U77-A1114-30L1
conn: UE75-A20-6000T

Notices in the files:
pico-pcm-cardem/pico-pcm-cardem.brd:
(c) 2023 sysmocom
rs422-protector/rs422_protect.brd:
(c) 20220 by Harald Welte
CC-BY-SA
sc14dect-breakout/sc14cvm-evb.brd:
(C) 2019 Harald Welte
sfp-breakout/sfp-experimenter.brd:
(C) 2018 sysmocom GmbH
License: CC-BY-SA
siu-clock-breakout/siu-clock-breakout.brd:
(C) 2020 by Harald Welte
xhfc-breakout/xhfc-breakout.brd:
(C) 2022 Harald Welte
parts and their libraries:
Wurth_Elektronik_Electromechanic_DC_Powe: Copyright: Würth Elektronik
